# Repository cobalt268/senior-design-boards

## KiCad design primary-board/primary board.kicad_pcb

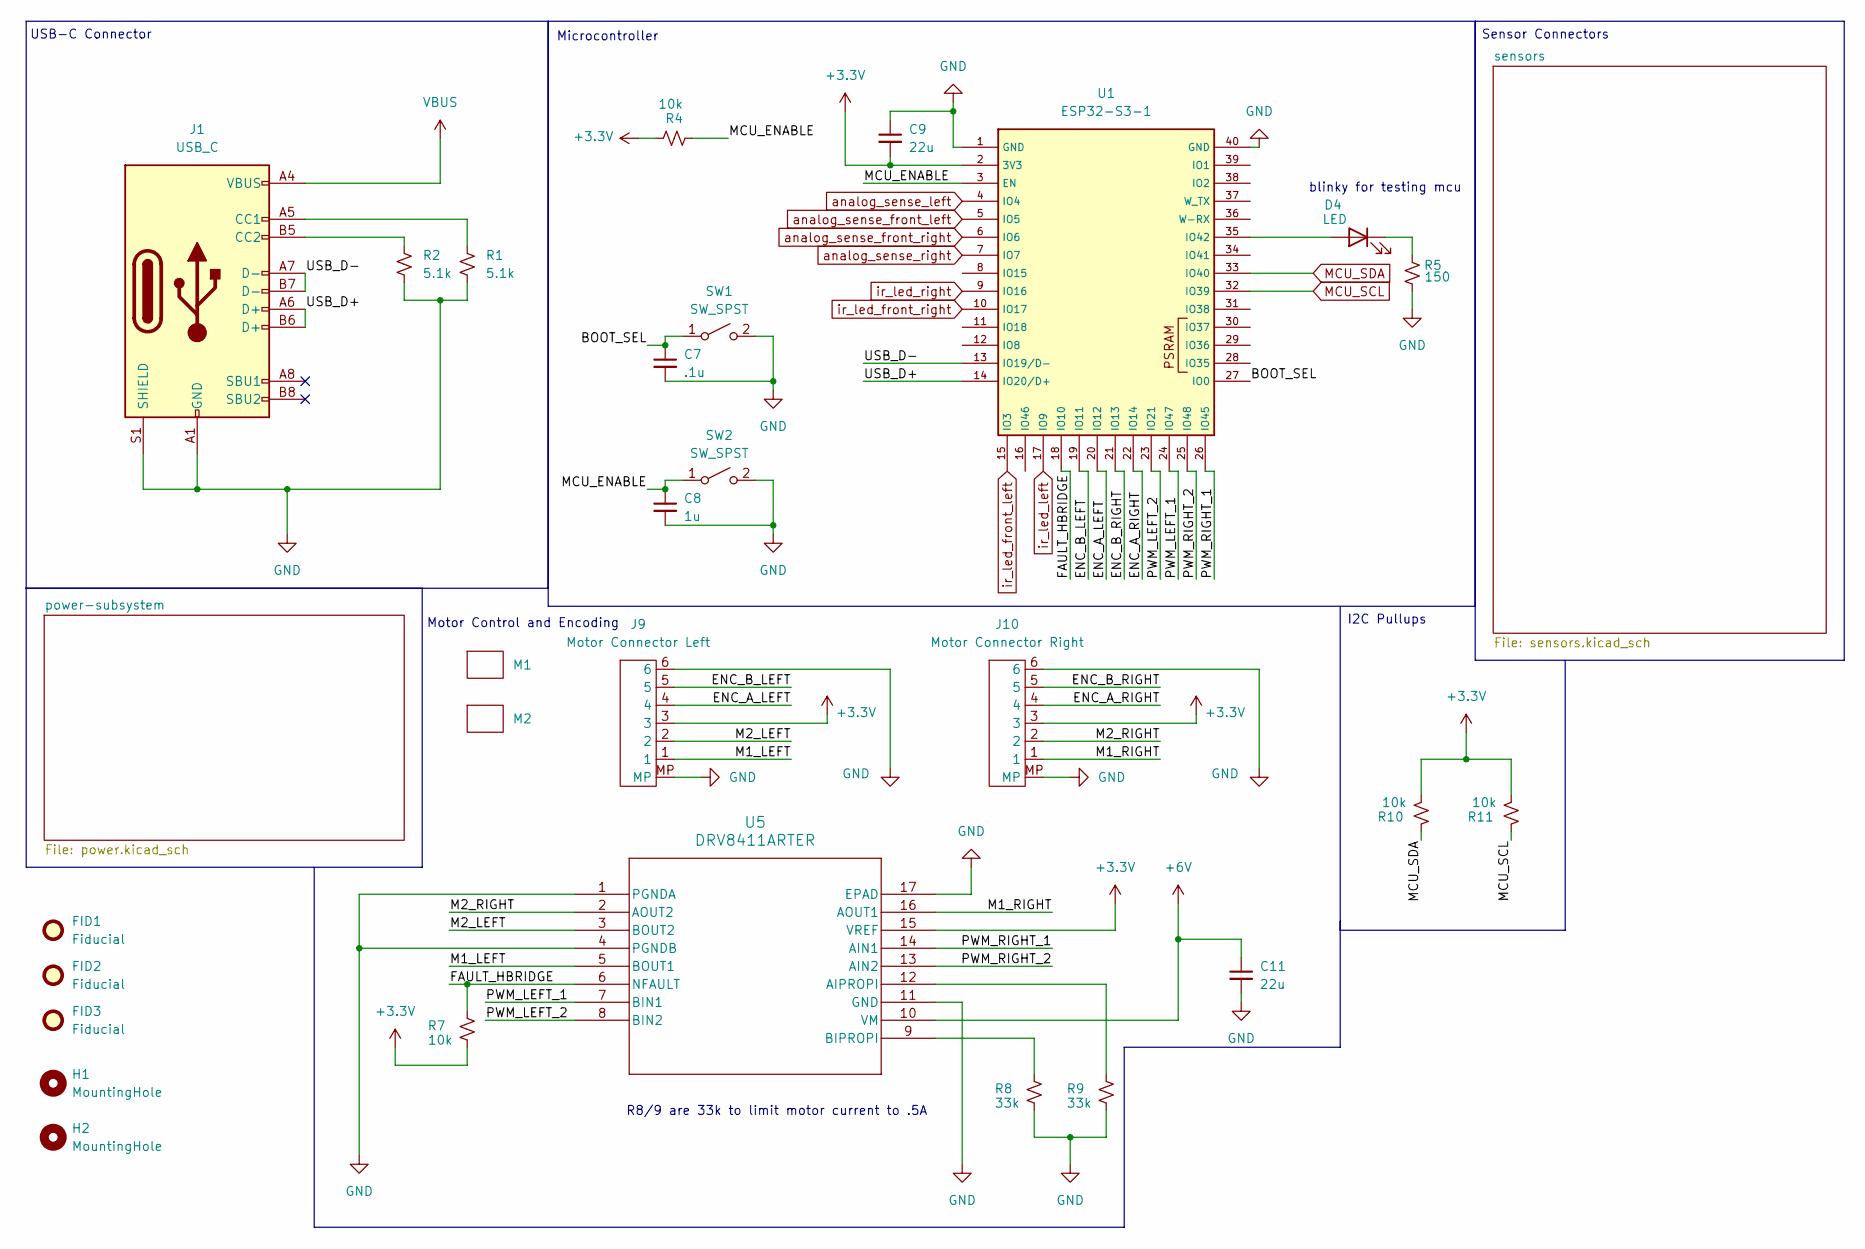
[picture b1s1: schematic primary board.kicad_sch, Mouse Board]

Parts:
C7: .1u; C_0603_1608Metric
C8: 1u; C_0603_1608Metric
C9, C11: 22u; C_0805_2012Metric
D4: LED; LED_0603_1608Metric
FID1, FID2, FID3: Fiducial; Fiducial_0.5mm_Mask1mm
H1, H2: MountingHole; MountingHole_2.2mm_M2
J1: USB_C; USB_C_Receptacle_GCT_USB4105-xx-A_16P_TopMnt_Horizontal
J9: Motor Connector Left; JST_SH_6_V
J10: Motor Connector Right; JST_SH_6_V
M1, M2: gearmotorenc
R1, R2: 5.1k; R_0603_1608Metric
R4, R7, R10, R11: 10k; R_0603_1608Metric
R5: 150; R_0603_1608Metric
R8, R9: 33k; R_0603_1608Metric_Pad0.98x0.95mm_HandSolder
SW1, SW2: SW_SPST; SW_SPST_Omron_B3FS-101xP
U1: ESP32-S3-1; ESP32-S3-1-WROOM_1
U5: DRV8411ARTER; WQFN16_RTE_TEX

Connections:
+3.3V: C9.2, J9.3, J10.3, R4.2, R7.2, R10.2, R11.2, U1.2 (3V3), U5.15 (VREF); also elsewhere on the board
+6V: C11.1, U5.10 (VM); also elsewhere on the board
/BOOT_SEL: C7.1, SW1.1 (A), U1.27 (IO0)
/ENC_A_LEFT: J9.4, U1.20 (IO12)
/ENC_A_RIGHT: J10.4, U1.22 (IO14)
/ENC_B_LEFT: J9.5, U1.19 (IO11)
/ENC_B_RIGHT: J10.5, U1.21 (IO13)
/FAULT_HBRIDGE: R7.1, U1.18 (IO10), U5.6 (NFAULT)
/M1_LEFT: J9.1, U5.5 (BOUT1)
/M1_RIGHT: J10.1, U5.16 (AOUT1)
/M2_LEFT: J9.2, U5.3 (BOUT2)
/M2_RIGHT: J10.2, U5.2 (AOUT2)
/MCU_ENABLE: C8.1, R4.1, SW2.1 (A), U1.3 (EN)
/PWM_LEFT_1: U1.24 (IO47), U5.7 (BIN1)
/PWM_LEFT_2: U1.23 (IO21), U5.8 (BIN2)
/PWM_RIGHT_1: U1.26 (IO45), U5.14 (AIN1)
/PWM_RIGHT_2: U1.25 (IO48), U5.13 (AIN2)
/USB_D+: J1.A6 (D+), J1.B6 (D+), U1.14 (IO20/D+)
/USB_D-: J1.A7 (D-), J1.B7 (D-), U1.13 (IO19/D-)
GND: C7.2, C8.2, C9.1, C11.2, J1.A1 (GND), J1.A12 (GND), J1.B1 (GND), J1.B12 (GND), J1.S1 (SHIELD), J9.6, J9.MP, J10.6, J10.MP, R1.1, R2.1, R5.1, R8.2, R9.2, SW1.2 (B), SW2.2 (B), U1.1 (GND), U1.40 (GND), U1.41 (GND__1), U5.1 (PGNDA), U5.4 (PGNDB), U5.11 (GND), U5.17 (EPAD); also elsewhere on the board
MCU_SCL: R11.1, U1.32 (IO39); also elsewhere on the board
MCU_SDA: R10.1, U1.33 (IO40); also elsewhere on the board
unnamed: D4.2 (A), U1.35 (IO42)
unnamed: D4.1 (K), R5.2
unnamed: J1.A5 (CC1), R1.2
unnamed: J1.B5 (CC2), R2.2
unnamed: R9.1, U5.12 (AIPROPI)
unnamed: R8.1, U5.9 (BIPROPI)
VBUS: J1.A4 (VBUS), J1.A9 (VBUS), J1.B4 (VBUS), J1.B9 (VBUS); also elsewhere on the board
analog_sense_front_left: U1.5 (IO5); also elsewhere on the board
analog_sense_front_right: U1.6 (IO6); also elsewhere on the board
analog_sense_left: U1.4 (IO4); also elsewhere on the board
analog_sense_right: U1.7 (IO7); also elsewhere on the board
ir_led_front_left: U1.15 (IO3); also elsewhere on the board
ir_led_front_right: U1.10 (IO17); also elsewhere on the board
ir_led_left: U1.17 (IO9); also elsewhere on the board
ir_led_right: U1.9 (IO16); also elsewhere on the board

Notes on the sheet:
blinky for testing mcu
I2C Pullups
Motor Control and Encoding
USB-C Connector
Sensor Connectors
Microcontroller
R8/9 are 33k to limit motor current to .5A

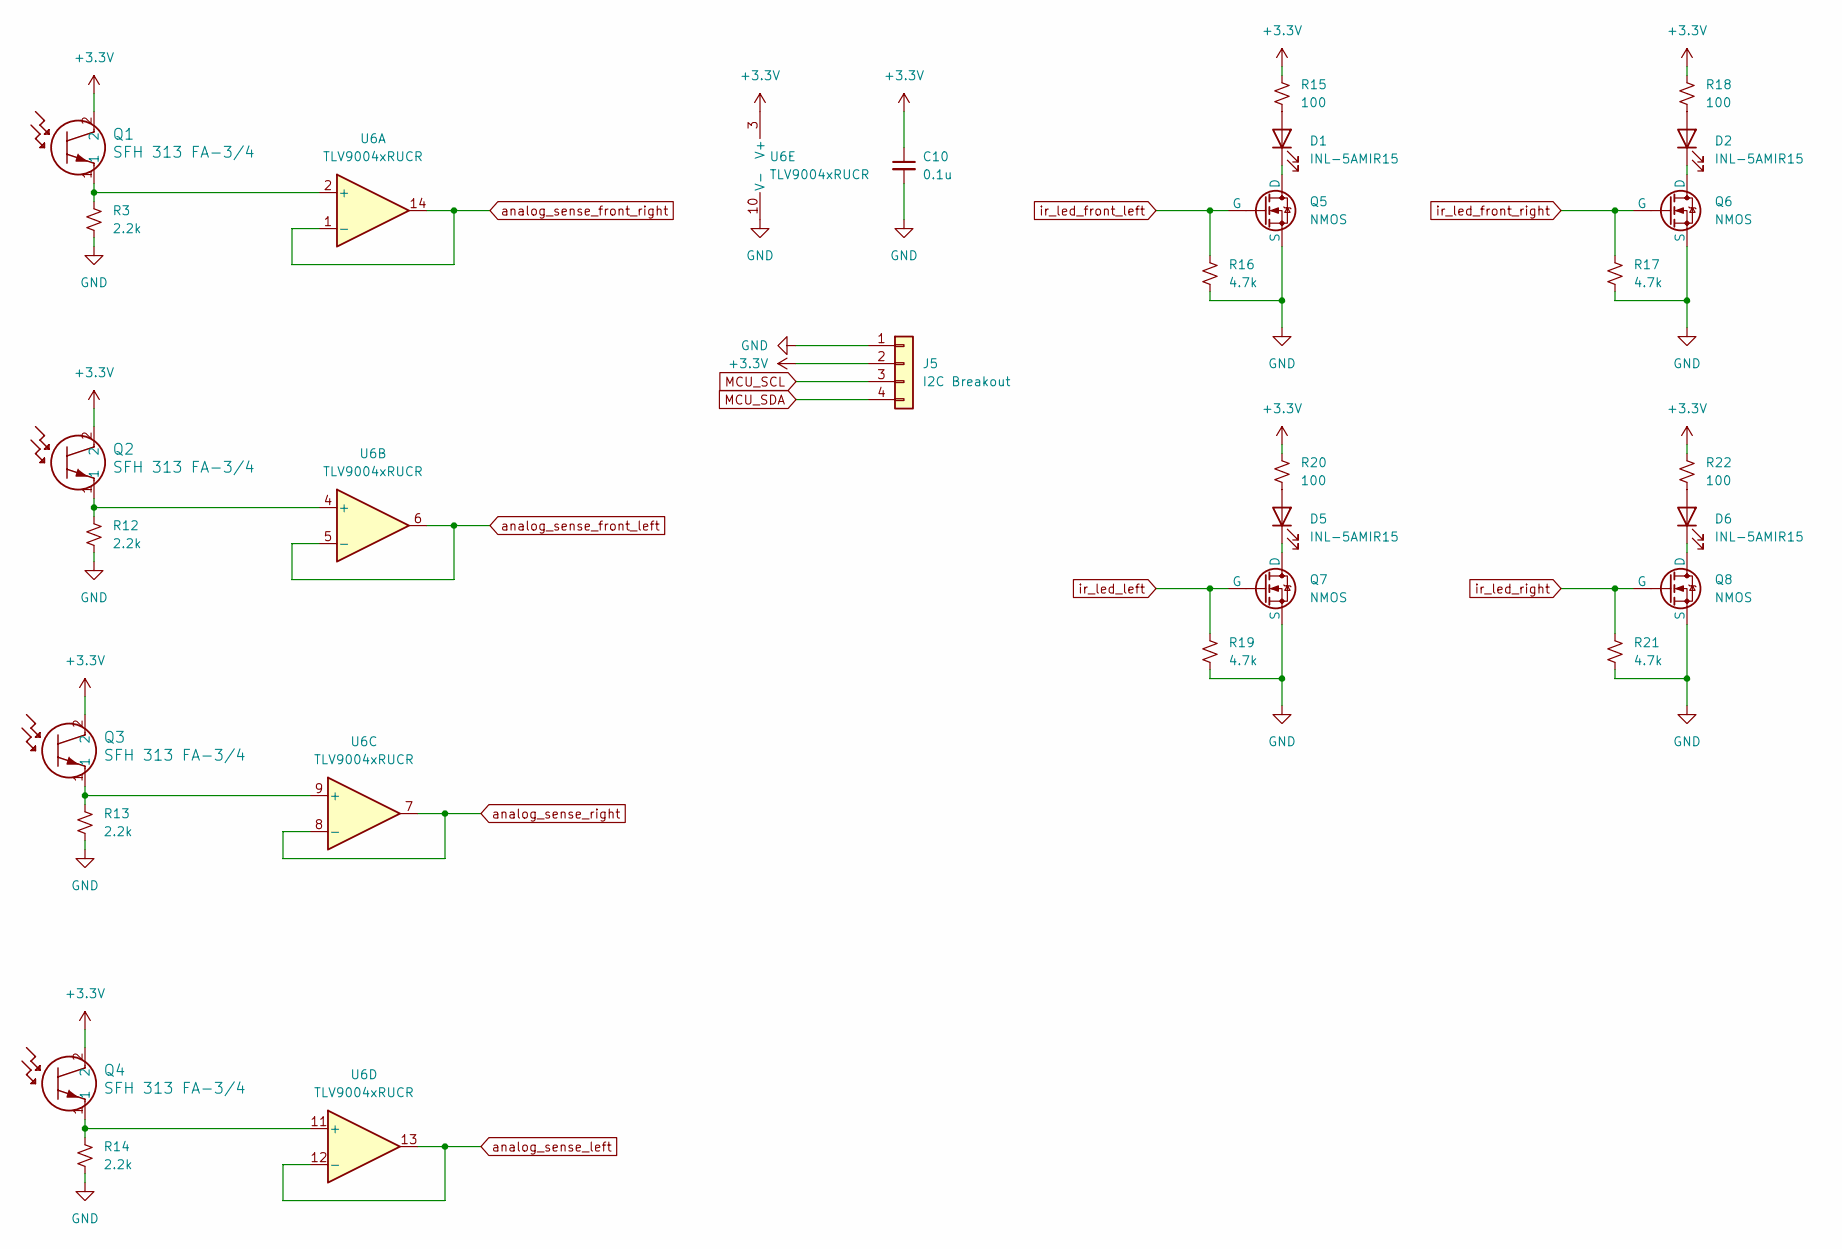
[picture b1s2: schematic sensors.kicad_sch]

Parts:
C10: 0.1u; C_0603_1608Metric
D1, D2, D5, D6: INL-5AMIR15; LED_D5.0mm_IRGrey
J5: I2C Breakout; PinSocket_1x04_P2.54mm_Vertical
Q1, Q2, Q3, Q4: SFH 313 FA-3/4; LED_D5.0mm_IRGrey
Q5, Q6, Q7, Q8: NMOS; SOT-23-3
R3, R12, R13, R14: 2.2k; R_0603_1608Metric
R15, R18, R20, R22: 100; R_0603_1608Metric
R16, R17, R19, R21: 4.7k; R_0603_1608Metric
U6: TLV9004xRUCR; Texas_S-PX2QFN-14

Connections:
+3.3V: C10.1, J5.2, Q1.2, Q2.2, Q3.2, Q4.2, R15.1, R18.1, R20.1, R22.1, U6.3 (V+); also elsewhere on the board
GND: C10.2, J5.1, Q5.3 (S), Q6.3 (S), Q7.3 (S), Q8.3 (S), R3.2, R12.2, R13.2, R14.2, R16.2, R17.2, R19.2, R21.2, U6.10 (V-); also elsewhere on the board
MCU_SCL: J5.3; also elsewhere on the board
MCU_SDA: J5.4; also elsewhere on the board
unnamed: D1.2 (A), R15.2
unnamed: D1.1 (K), Q5.1 (D)
unnamed: D2.2 (A), R18.2
unnamed: D2.1 (K), Q6.1 (D)
unnamed: D5.2 (A), R20.2
unnamed: D5.1 (K), Q7.1 (D)
unnamed: D6.2 (A), R22.2
unnamed: D6.1 (K), Q8.1 (D)
unnamed: Q1.1, R3.1, U6.2 (+)
unnamed: Q2.1, R12.1, U6.4 (+)
unnamed: Q3.1, R13.1, U6.9 (+)
unnamed: Q4.1, R14.1, U6.11 (+)
analog_sense_front_left: U6.5 (-), U6.6; also elsewhere on the board
analog_sense_front_right: U6.1 (-), U6.14; also elsewhere on the board
analog_sense_left: U6.12 (-), U6.13; also elsewhere on the board
analog_sense_right: U6.7, U6.8 (-); also elsewhere on the board
ir_led_front_left: Q5.2 (G), R16.1; also elsewhere on the board
ir_led_front_right: Q6.2 (G), R17.1; also elsewhere on the board
ir_led_left: Q7.2 (G), R19.1; also elsewhere on the board
ir_led_right: Q8.2 (G), R21.1; also elsewhere on the board

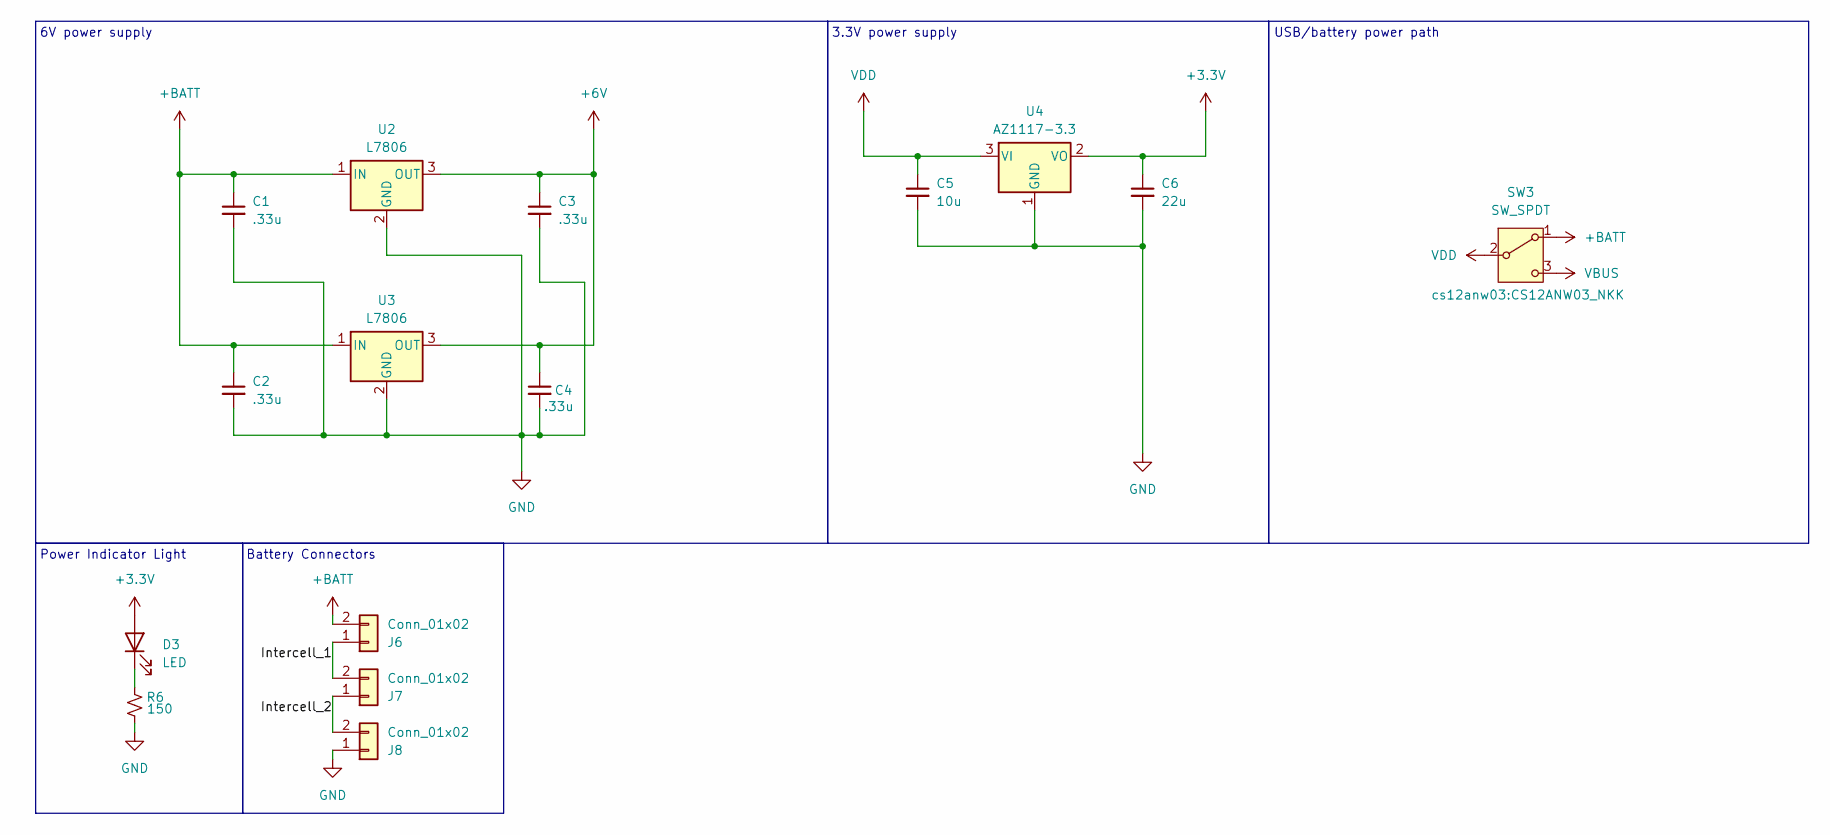
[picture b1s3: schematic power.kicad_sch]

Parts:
C1, C2, C3, C4: .33u; C_0603_1608Metric
C5: 10u; C_0805_2012Metric
C6: 22u; C_0805_2012Metric
D3: LED; LED_0603_1608Metric
J6, J7, J8: Conn_01x02; JST_PH_B2B-PH-K_1x02_P2.00mm_Vertical
R6: 150; R_0603_1608Metric
SW3: SW_SPDT; CS12ANW03_NKK
U2, U3: L7806; TO-263-2
U4: AZ1117-3.3; SOT-223-3_TabPin2

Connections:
+3.3V: C6.1, D3.2 (A), U4.2 (VO); also elsewhere on the board
+6V: C3.1, C4.1, U2.3 (OUT), U3.3 (OUT); also elsewhere on the board
+BATT: C1.1, C2.1, J6.2, SW3.1 (A), U2.1 (IN), U3.1 (IN)
/power-subsystem/Intercell_1: J6.1, J7.2
/power-subsystem/Intercell_2: J7.1, J8.2
GND: C1.2, C2.2, C3.2, C4.2, C5.2, C6.2, J8.1, R6.1, U2.2 (GND), U3.2 (GND), U4.1 (GND); also elsewhere on the board
unnamed: D3.1 (K), R6.2
VBUS: SW3.3 (C); also elsewhere on the board
VDD: C5.1, SW3.2 (B), U4.3 (VI)

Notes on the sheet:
3.3V power supply
USB/battery power path
Battery Connectors
Power Indicator Light
6V power supply

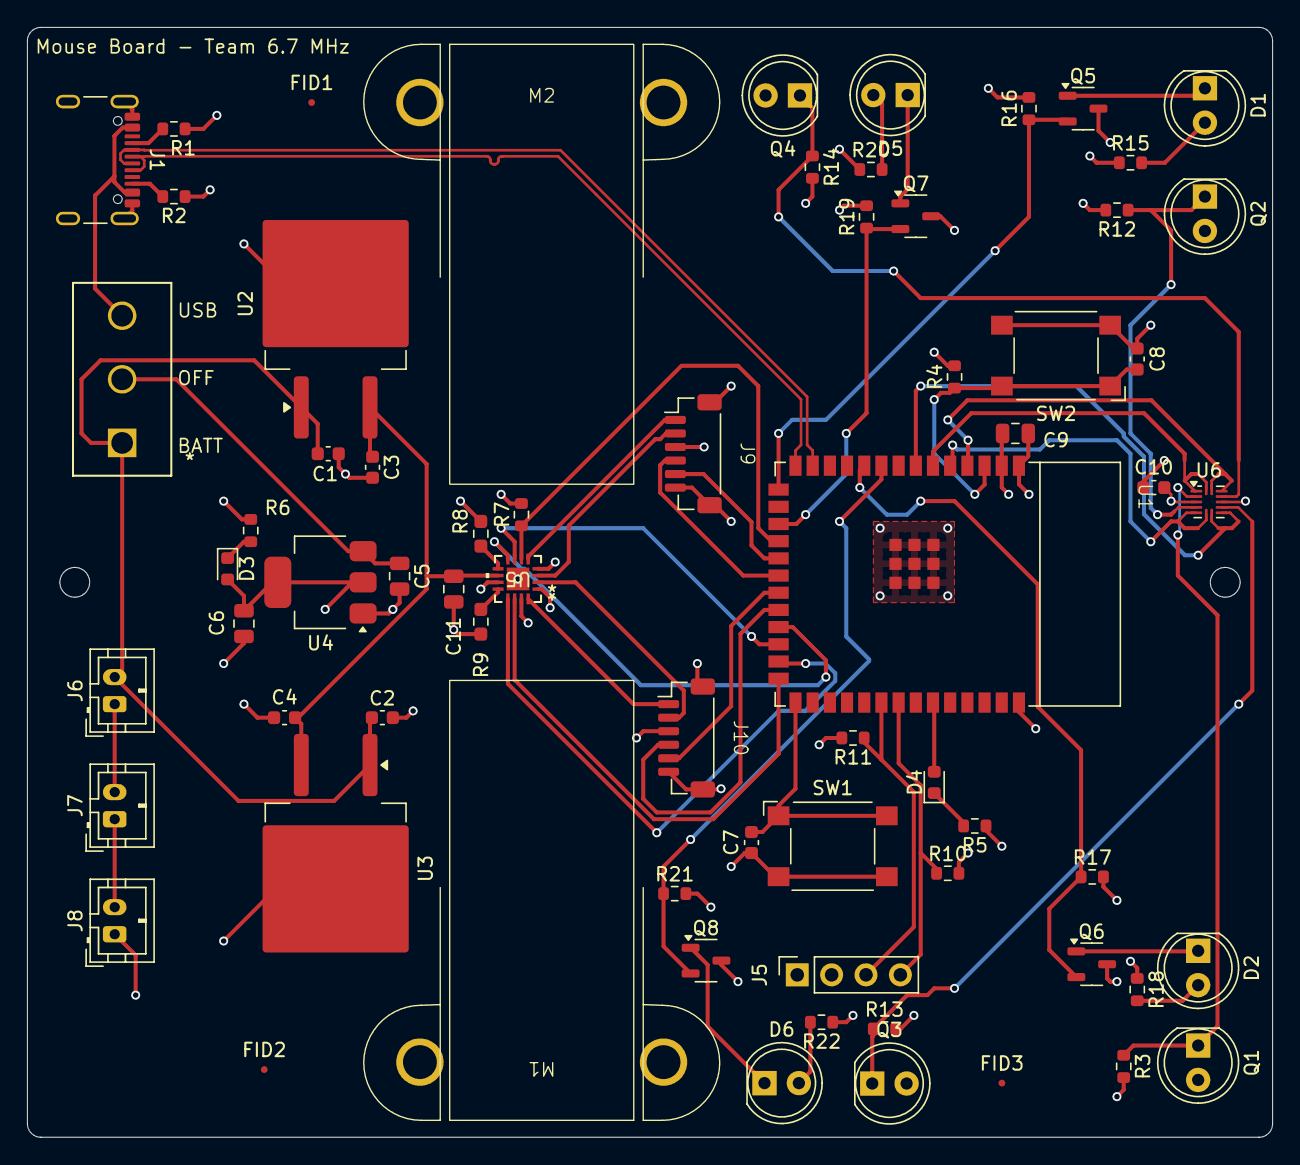
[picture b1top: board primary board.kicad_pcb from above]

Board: 4 copper layers, 92.0 x 82.0 mm, 70 parts (0 on the bottom side), 54 nets.

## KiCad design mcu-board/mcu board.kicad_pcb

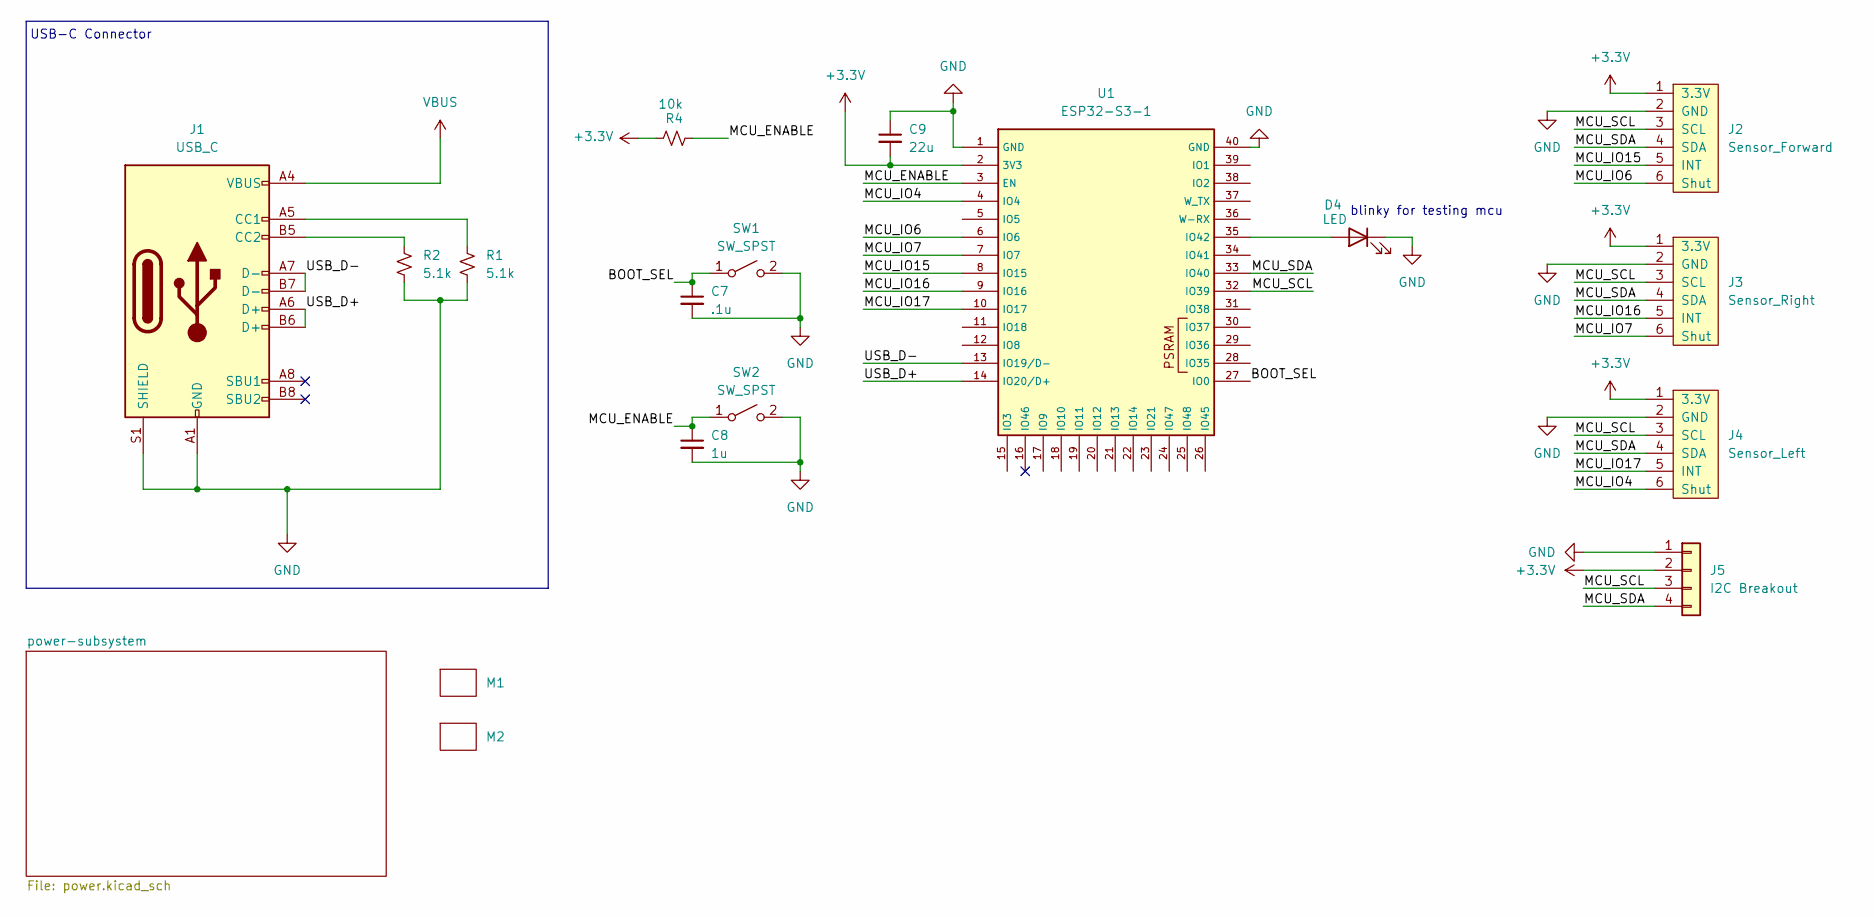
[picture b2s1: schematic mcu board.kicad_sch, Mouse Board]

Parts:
C7: .1u; C_0603_1608Metric
C8: 1u; C_0603_1608Metric
C9: 22u; C_0805_2012Metric
D4: LED; LED_0603_1608Metric
J1: USB_C; USB_C_Receptacle_GCT_USB4105-xx-A_16P_TopMnt_Horizontal
J2: Sensor_Forward; PinSocket_1x06_P2.54mm_Vertical
J3: Sensor_Right; PinSocket_1x06_P2.54mm_Vertical
J4: Sensor_Left; PinSocket_1x06_P2.54mm_Vertical
J5: I2C Breakout; PinSocket_1x04_P2.54mm_Vertical
M1, M2: gearmotorenc
R1, R2: 5.1k; R_0603_1608Metric
R4: 10k; R_0603_1608Metric
SW1, SW2: SW_SPST; SW_TH_Tactile_Omron_B3F-100x
U1: ESP32-S3-1; ESP32-S3-1-WROOM_1

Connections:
+3.3V: C9.2, J2.1 (3.3V), J3.1 (3.3V), J4.1 (3.3V), J5.2, R4.2, U1.2 (3V3); also elsewhere on the board
/BOOT_SEL: C7.1, SW1.1 (A), U1.27 (IO0)
/MCU_ENABLE: C8.1, R4.1, SW2.1 (A), U1.3 (EN)
/MCU_IO4: J4.6 (Shut), U1.4 (IO4)
/MCU_IO6: J2.6 (Shut), U1.6 (IO6)
/MCU_IO7: J3.6 (Shut), U1.7 (IO7)
/MCU_IO15: J2.5 (INT), U1.8 (IO15)
/MCU_IO16: J3.5 (INT), U1.9 (IO16)
/MCU_IO17: J4.5 (INT), U1.10 (IO17)
/MCU_SCL: J2.3 (SCL), J3.3 (SCL), J4.3 (SCL), J5.3, U1.32 (IO39)
/MCU_SDA: J2.4 (SDA), J3.4 (SDA), J4.4 (SDA), J5.4, U1.33 (IO40)
/USB_D+: J1.A6 (D+), J1.B6 (D+), U1.14 (IO20/D+)
/USB_D-: J1.A7 (D-), J1.B7 (D-), U1.13 (IO19/D-)
GND: C7.2, C8.2, C9.1, D4.1 (K), J1.A1 (GND), J1.A12 (GND), J1.B1 (GND), J1.B12 (GND), J1.S1 (SHIELD), J2.2 (GND), J3.2 (GND), J4.2 (GND), J5.1, R1.1, R2.1, SW1.2 (B), SW2.2 (B), U1.1 (GND), U1.40 (GND), U1.41 (GND__1); also elsewhere on the board
unnamed: D4.2 (A), U1.35 (IO42)
unnamed: J1.A5 (CC1), R1.2
unnamed: J1.B5 (CC2), R2.2
VBUS: J1.A4 (VBUS), J1.A9 (VBUS), J1.B4 (VBUS), J1.B9 (VBUS); also elsewhere on the board

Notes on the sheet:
blinky for testing mcu
USB-C Connector

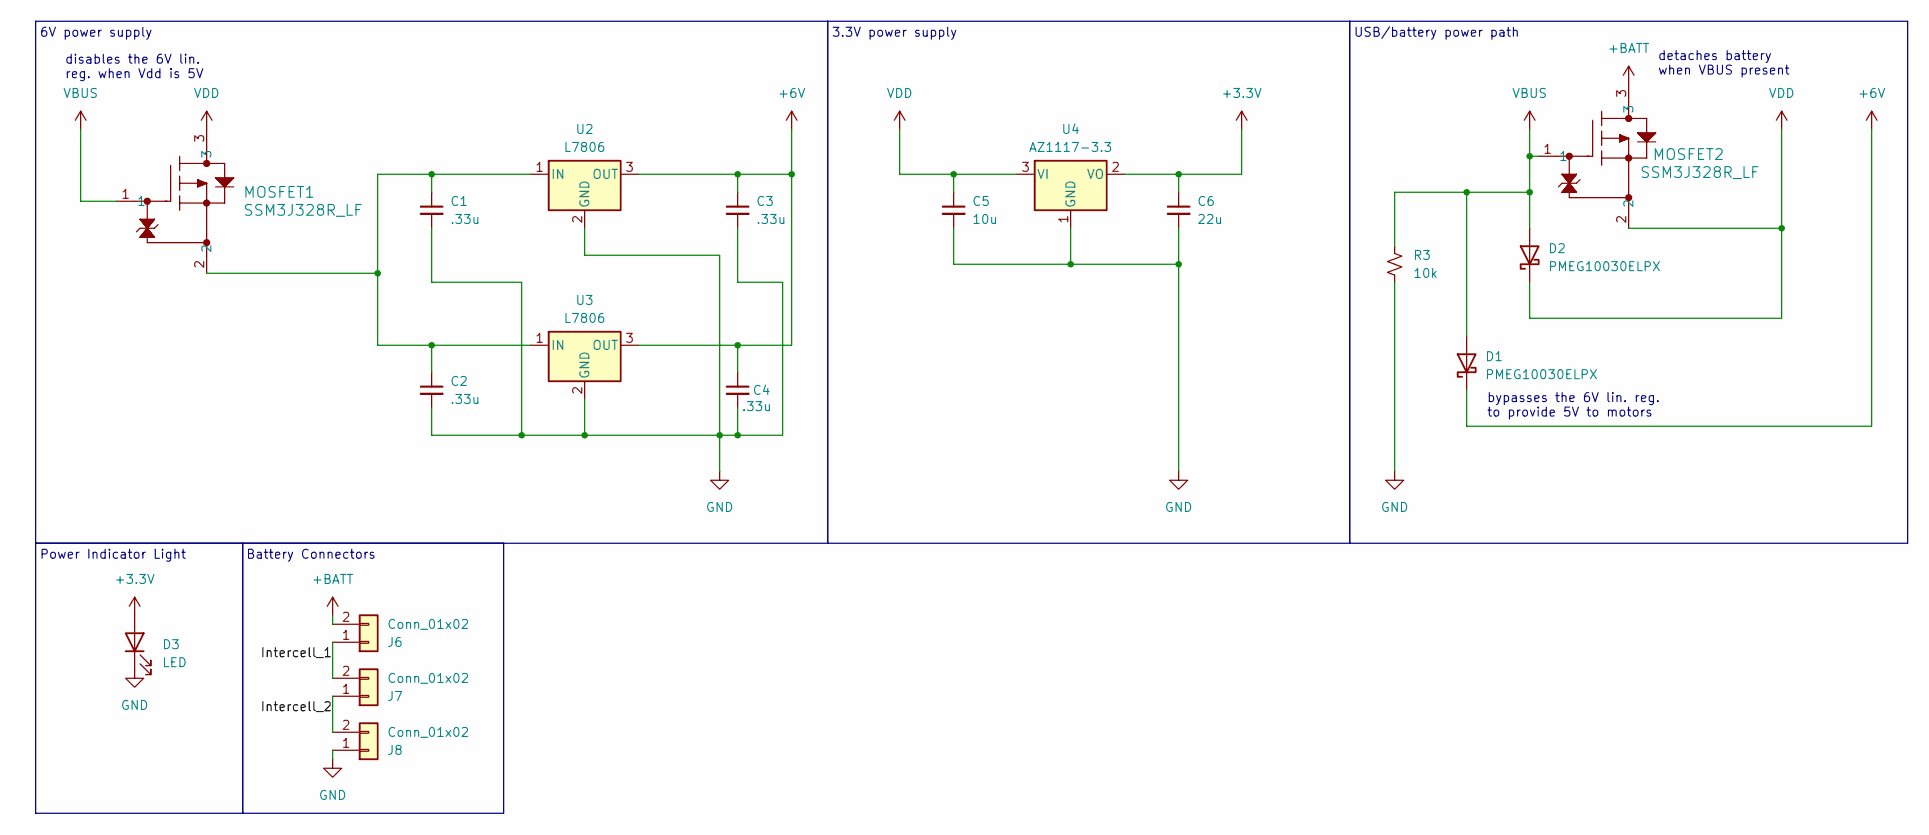
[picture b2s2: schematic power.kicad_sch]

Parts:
C1, C2, C3, C4: .33u; C_0603_1608Metric
C5: 10u; C_0805_2012Metric
C6: 22u; C_0805_2012Metric
D1, D2: PMEG10030ELPX; D_SOD-128
D3: LED; LED_0603_1608Metric
J6, J7, J8: Conn_01x02; JST_PH_B2B-PH-K_1x02_P2.00mm_Vertical
MOSFET1, MOSFET2: SSM3J328R_LF; SOT-23F_TOS
R3: 10k; R_0603_1608Metric
U2, U3: L7806; TO-263-2
U4: AZ1117-3.3; SOT-223-3_TabPin2

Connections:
+3.3V: C6.1, D3.2 (A), U4.2 (VO); also elsewhere on the board
+6V: C3.1, C4.1, D1.1 (K), U2.3 (OUT), U3.3 (OUT)
+BATT: J6.2, MOSFET2.3
/power-subsystem/Intercell_1: J6.1, J7.2
/power-subsystem/Intercell_2: J7.1, J8.2
GND: C1.2, C2.2, C3.2, C4.2, C5.2, C6.2, D3.1 (K), J8.1, R3.2, U2.2 (GND), U3.2 (GND), U4.1 (GND); also elsewhere on the board
unnamed: C1.1, C2.1, MOSFET1.2, U2.1 (IN), U3.1 (IN)
VBUS: D1.2 (A), D2.2 (A), MOSFET1.1, MOSFET2.1, R3.1; also elsewhere on the board
VDD: C5.1, D2.1 (K), MOSFET1.3, MOSFET2.2, U4.3 (VI)

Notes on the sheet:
3.3V power supply
detaches battery when VBUS present
USB/battery power path
disables the 6V lin. reg. when Vdd is 5V
Battery Connectors
Power Indicator Light
bypasses the 6V lin. reg. to provide 5V to motors
6V power supply

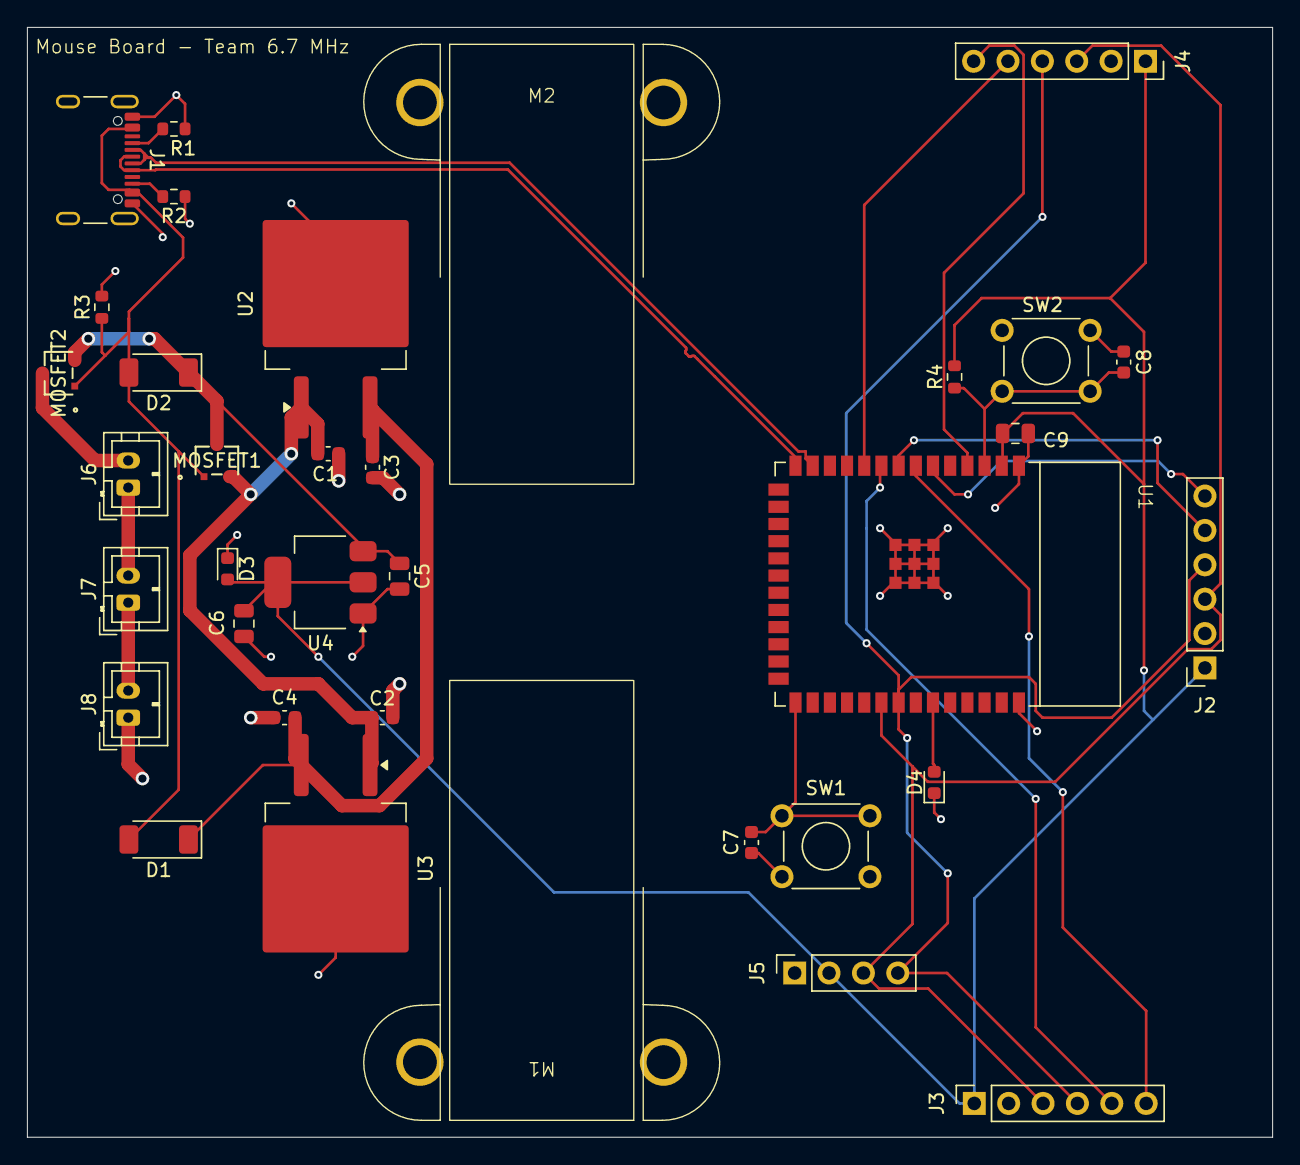
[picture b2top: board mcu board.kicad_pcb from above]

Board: 4 copper layers, 92.0 x 82.0 mm, 35 parts (0 on the bottom side), 24 nets.

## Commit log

2025-11-17 repo init
2025-11-17 added libs
2025-11-18 renamed directory
2025-11-18 removed lock
2025-11-18 gitignore made
2025-11-18 added usb-c, power, started on mcu
2025-11-19 finished schematic(?)
2025-11-20 footprints
2025-11-20 pcb routed
2026-03-20 dante review
